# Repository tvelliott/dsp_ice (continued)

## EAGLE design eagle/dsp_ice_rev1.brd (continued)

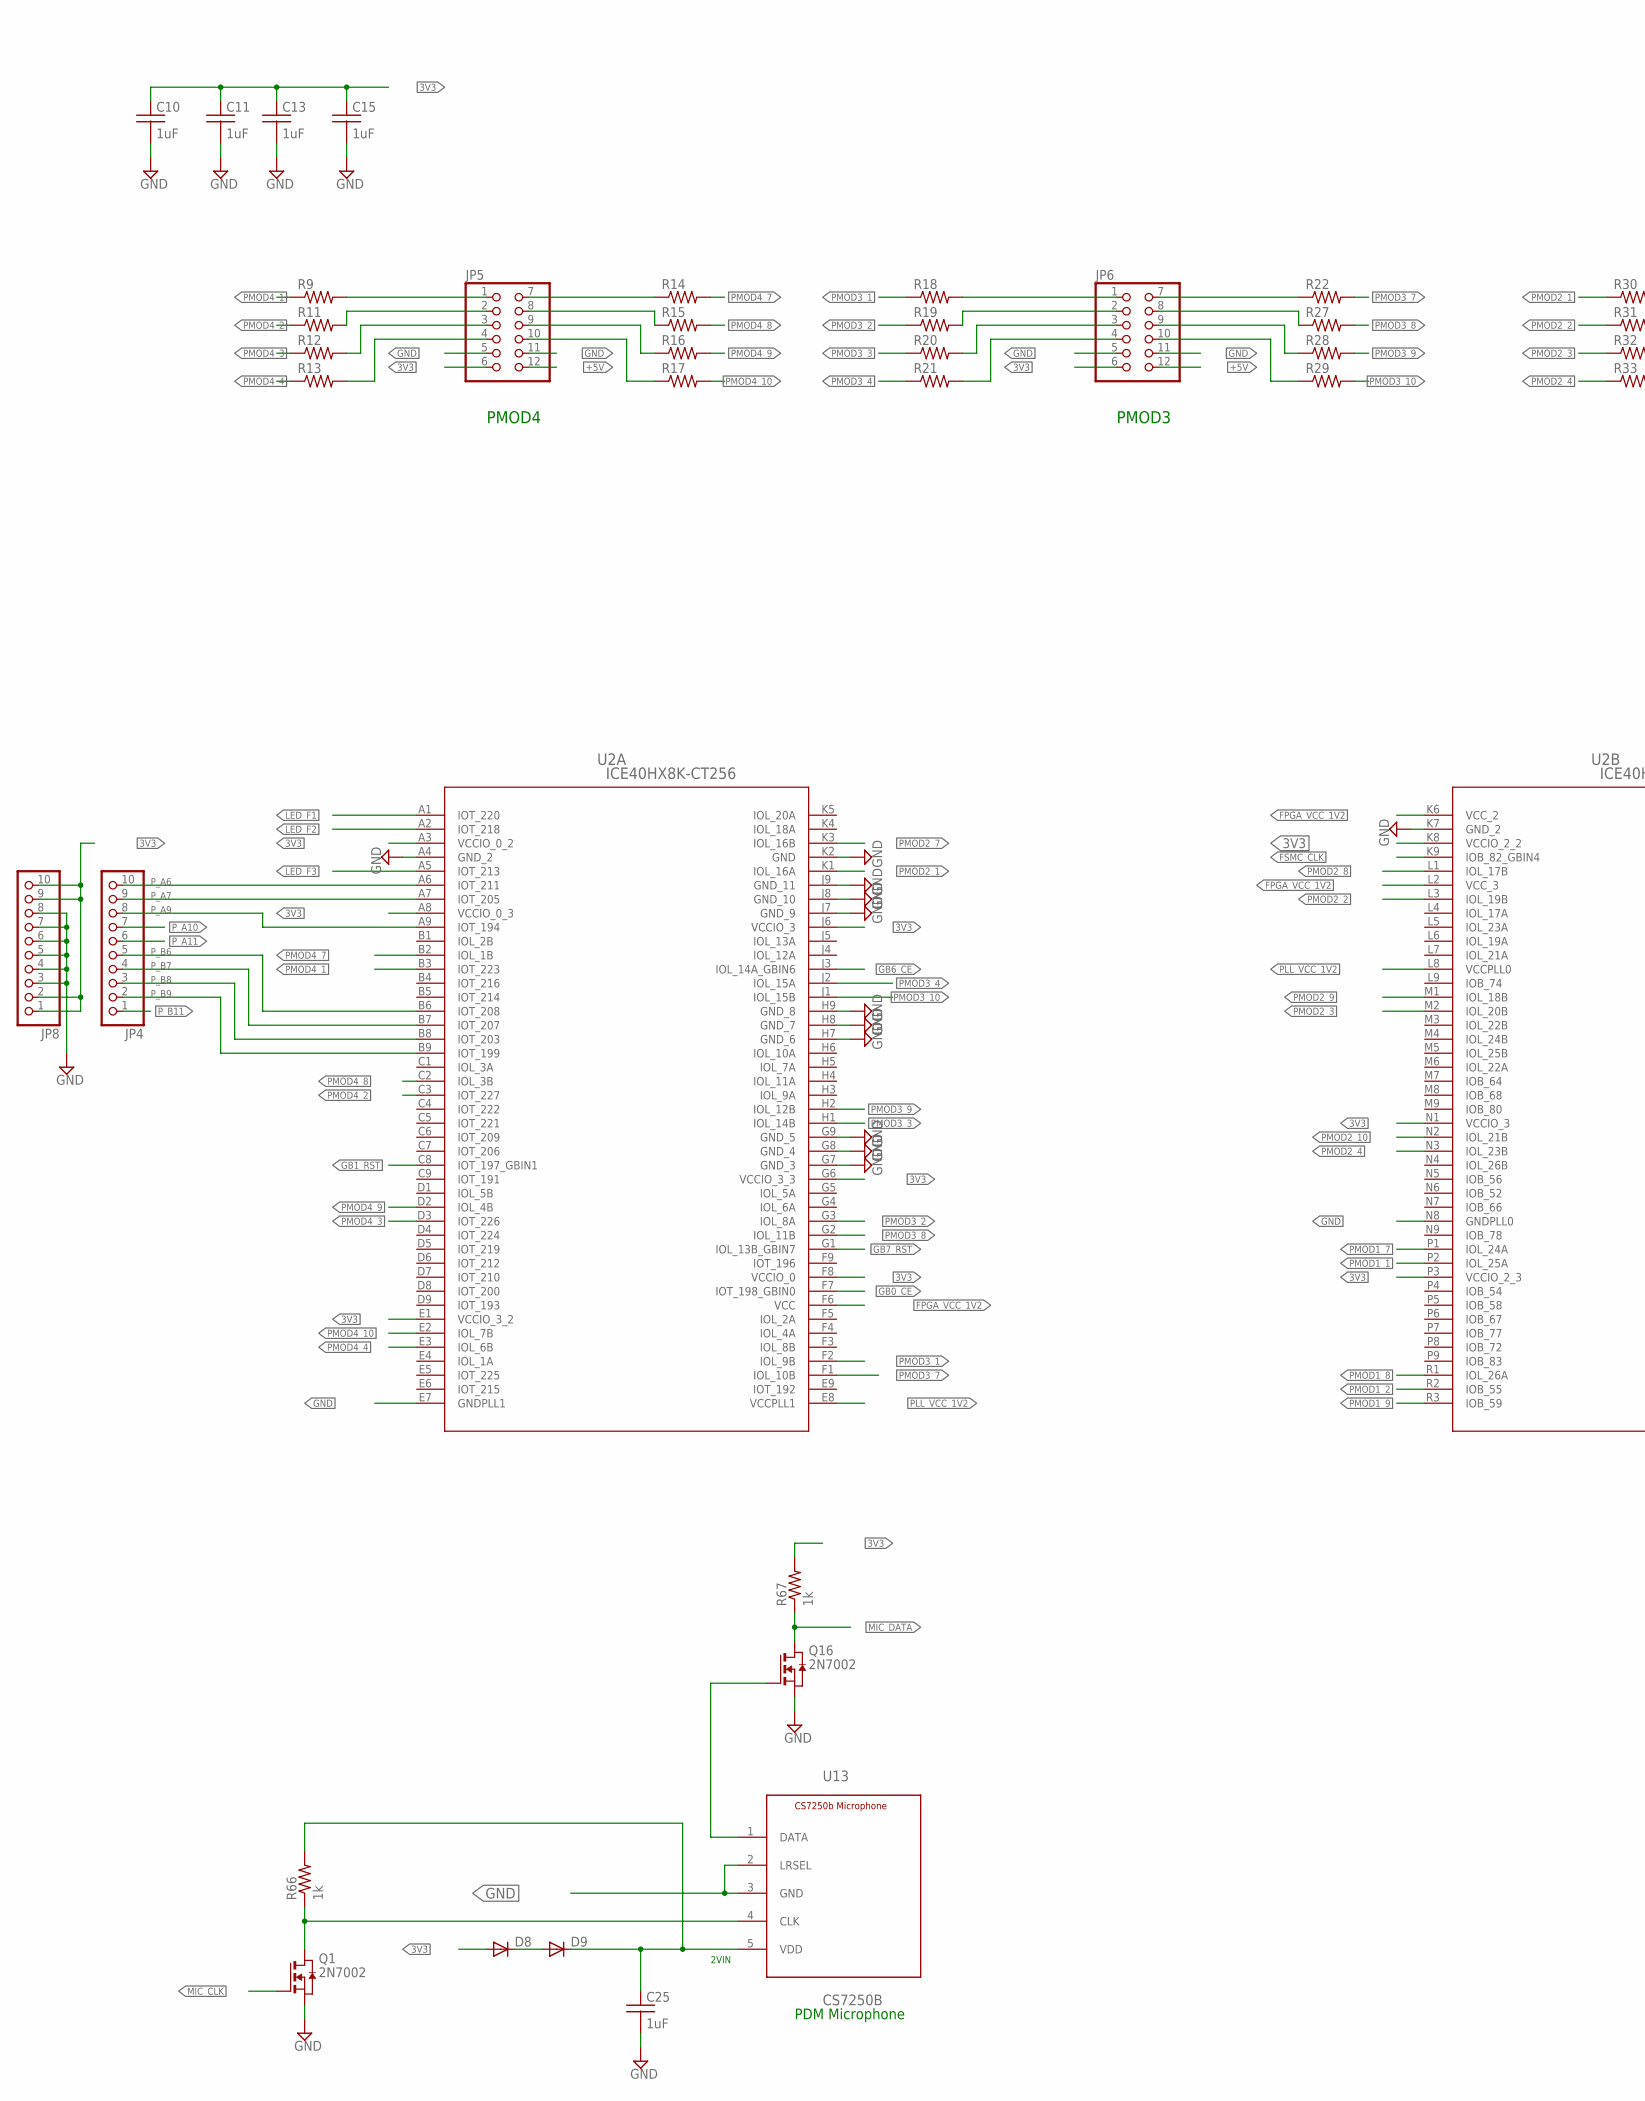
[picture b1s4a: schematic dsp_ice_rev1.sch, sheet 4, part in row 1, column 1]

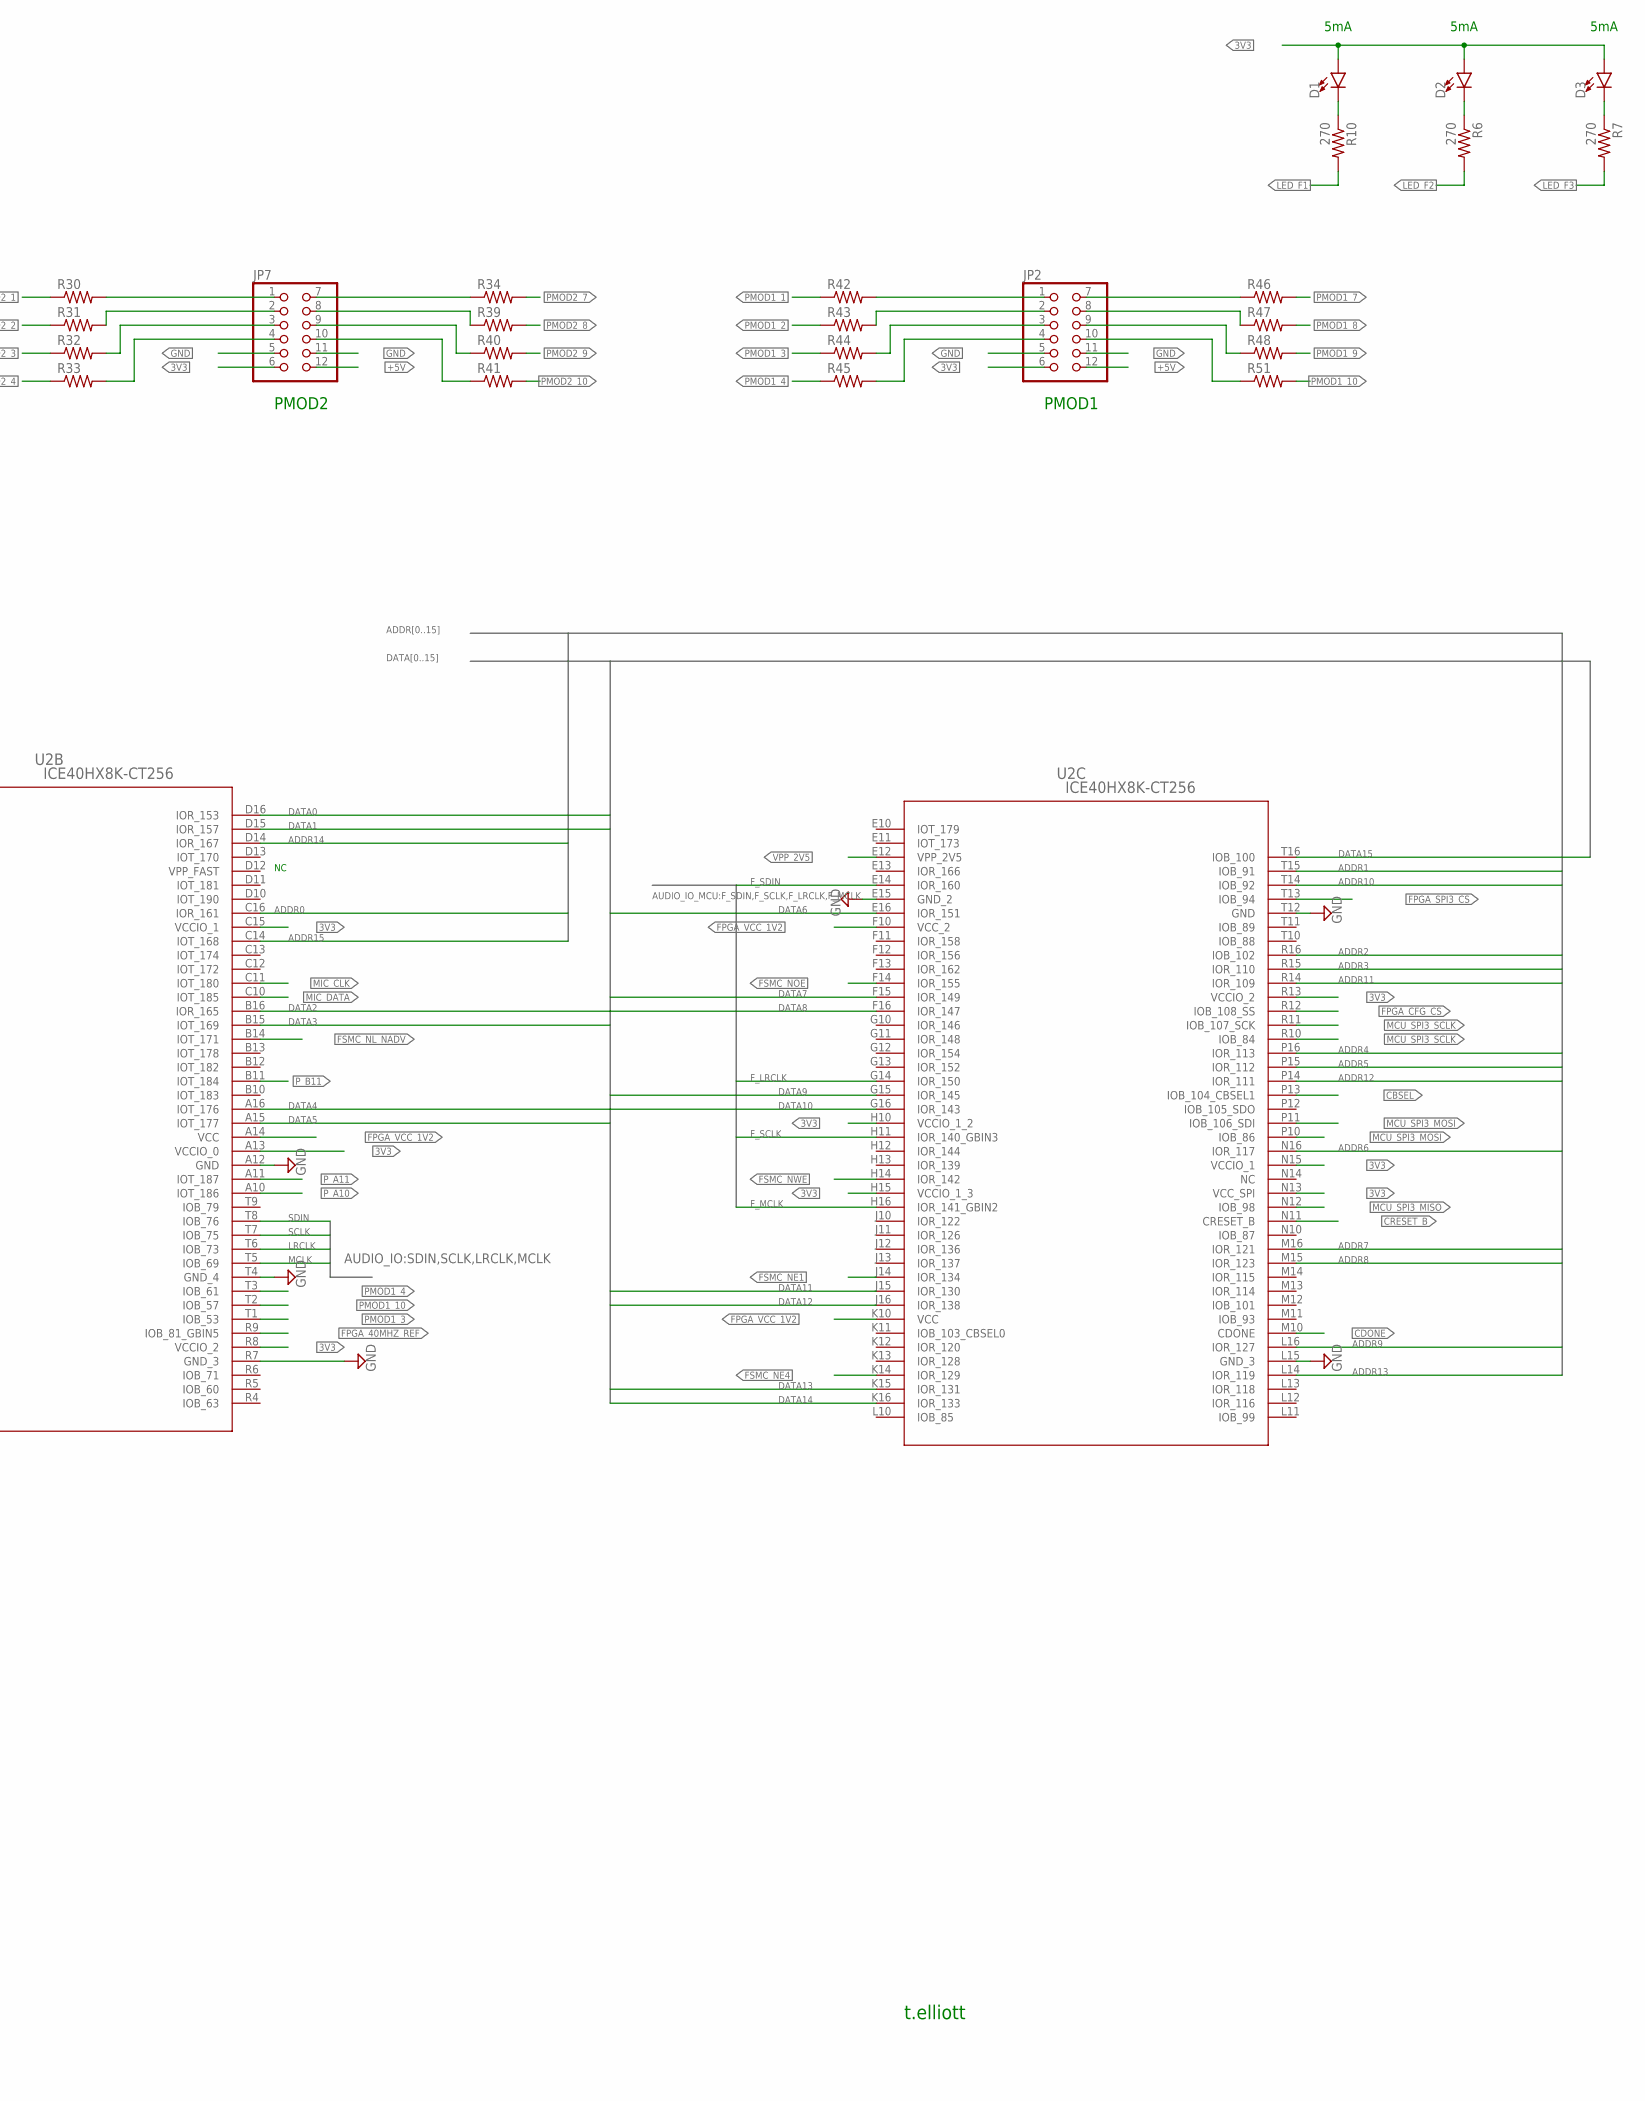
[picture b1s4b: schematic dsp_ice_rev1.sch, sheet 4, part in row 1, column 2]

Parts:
C10, C11, C13, C15, C25: 1uF; C0603
D1, D2, D3: LED1206; LED-1206
D8, D9: DIODE-MINIMELF; MINIMELF
JP2, JP5, JP6, JP7: PINHD-2X6; 2X06
JP4, JP8: PINHD-1X10; 1X10
Q1, Q16: 2N7002; SOT23_2N7002_PACKAGE
R6, R7, R10: 270; R0603
R9, R11, R12, R13, R14, R15, R16, R17, R18, R19, R20, R21, R22, R27, R28, R29, R30, R31, R32, R33, R34, R39, R40, R41, R42, R43, R44, R45, R46, R47, R48, R51: 10; R0603
R66, R67: 1k; R0603
U2: ICE40HX8K-CT256; CABGA256
U13: CS7250B; CS7250B-CAZR

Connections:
3V3: C10.1, C11.1, C13.1, C15.1, D1.A, D2.A, D3.A, D8.A, JP2.6 (11), JP5.6 (11), JP6.6 (11), JP7.6 (11), JP8.1, JP8.2, JP8.9, JP8.10, R67.2, U2.A3 (VCCIO_0_2), U2.A8 (VCCIO_0_3), U2.A13 (VCCIO_0), U2.C15 (VCCIO_1), U2.E1 (VCCIO_3_2), U2.F8 (VCCIO_0), U2.G6 (VCCIO_3_3), U2.H10 (VCCIO_1_2), U2.H15 (VCCIO_1_3), U2.J6 (VCCIO_3), U2.K8 (VCCIO_2_2), U2.N1 (VCCIO_3), U2.N13 (VCC_SPI), U2.N15 (VCCIO_1), U2.P3 (VCCIO_2_3), U2.R8 (VCCIO_2), U2.R13 (VCCIO_2); also elsewhere on the board
+5V: JP2.12, JP5.12, JP6.12, JP7.12; also elsewhere on the board
ADDR0: U2.C16 (IOR_161); also elsewhere on the board
ADDR1: U2.T15 (IOB_91); also elsewhere on the board
ADDR2: U2.R16 (IOB_102); also elsewhere on the board
ADDR3: U2.R15 (IOR_110); also elsewhere on the board
ADDR4: U2.P16 (IOR_113); also elsewhere on the board
ADDR5: U2.P15 (IOR_112); also elsewhere on the board
ADDR6: U2.N16 (IOR_117); also elsewhere on the board
ADDR7: U2.M16 (IOR_121); also elsewhere on the board
ADDR8: U2.M15 (IOR_123); also elsewhere on the board
ADDR9: U2.L16 (IOR_127); also elsewhere on the board
ADDR10: U2.T14 (IOB_92); also elsewhere on the board
ADDR11: U2.R14 (IOR_109); also elsewhere on the board
ADDR12: U2.P14 (IOR_111); also elsewhere on the board
ADDR13: U2.L14 (IOR_119); also elsewhere on the board
ADDR14: U2.D14 (IOR_167); also elsewhere on the board
ADDR15: U2.C14 (IOT_168); also elsewhere on the board
CBSEL: U2.P13 (IOB_104_CBSEL1); also elsewhere on the board
CDONE: U2.M10 (CDONE); also elsewhere on the board
CRESET_B: U2.N11 (CRESET_B); also elsewhere on the board
DATA0: U2.D16 (IOR_153); also elsewhere on the board
DATA1: U2.D15 (IOR_157); also elsewhere on the board
DATA2: U2.B16 (IOR_165); also elsewhere on the board
DATA3: U2.B15 (IOT_169); also elsewhere on the board
DATA4: U2.A16 (IOT_176); also elsewhere on the board
DATA5: U2.A15 (IOT_177); also elsewhere on the board
DATA6: U2.E16 (IOR_151); also elsewhere on the board
DATA7: U2.F15 (IOR_149); also elsewhere on the board
DATA8: U2.F16 (IOR_147); also elsewhere on the board
DATA9: U2.G15 (IOR_145); also elsewhere on the board
DATA10: U2.G16 (IOR_143); also elsewhere on the board
DATA11: U2.J15 (IOR_130); also elsewhere on the board
DATA12: U2.J16 (IOR_138); also elsewhere on the board
DATA13: U2.K15 (IOR_131); also elsewhere on the board
DATA14: U2.K16 (IOR_133); also elsewhere on the board
DATA15: U2.T16 (IOB_100); also elsewhere on the board
FPGA_40MHZ_REF: U2.R9 (IOB_81_GBIN5); also elsewhere on the board
FPGA_CFG_CS: U2.R12 (IOB_108_SS); also elsewhere on the board
FPGA_SPI3_CS: U2.T13 (IOB_94); also elsewhere on the board
FPGA_VCC_1V2: U2.A14 (VCC), U2.F6 (VCC), U2.F10 (VCC_2), U2.K6 (VCC_2), U2.K10 (VCC), U2.L2 (VCC_3); also elsewhere on the board
FSMC_CLK: U2.K9 (IOB_82_GBIN4); also elsewhere on the board
FSMC_NE1: U2.J14 (IOR_134); also elsewhere on the board
FSMC_NE4: U2.K14 (IOR_129); also elsewhere on the board
FSMC_NL_NADV: U2.B14 (IOT_171); also elsewhere on the board
FSMC_NOE: U2.F14 (IOR_155); also elsewhere on the board
FSMC_NWE: U2.H14 (IOR_142); also elsewhere on the board
F_LRCLK: U2.G14 (IOR_150); also elsewhere on the board
F_MCLK: U2.H16 (IOR_141_GBIN2); also elsewhere on the board
F_SCLK: U2.H11 (IOR_140_GBIN3); also elsewhere on the board
F_SDIN: U2.E14 (IOR_160); also elsewhere on the board
GB0_CE: U2.F7 (IOT_198_GBIN0)
GB1_RST: U2.C8 (IOT_197_GBIN1)
GB6_CE: U2.J3 (IOL_14A_GBIN6)
GB7_RST: U2.G1 (IOL_13B_GBIN7)
GND: C10.2, C11.2, C13.2, C15.2, C25.2, JP2.5 (9), JP2.11 (10), JP5.5 (9), JP5.11 (10), JP6.5 (9), JP6.11 (10), JP7.5 (9), JP7.11 (10), JP8.3, JP8.4, JP8.5, JP8.6, JP8.7, JP8.8, Q1.2 (S), Q16.2 (S), U2.A4 (GND_2), U2.A12 (GND), U2.E7 (GNDPLL1), U2.E15 (GND_2), U2.G7 (GND_3), U2.G8 (GND_4), U2.G9 (GND_5), U2.H7 (GND_6), U2.H8 (GND_7), U2.H9 (GND_8), U2.J7 (GND_9), U2.J8 (GND_10), U2.J9 (GND_11), U2.K2 (GND), U2.K7 (GND_2), U2.L15 (GND_3), U2.N8 (GNDPLL0), U2.R7 (GND_3), U2.T4 (GND_4), U2.T12 (GND), U13.2 (LRSEL), U13.3 (GND); also elsewhere on the board
LED_F1: R10.2, U2.A1 (IOT_220)
LED_F2: R6.2, U2.A2 (IOT_218)
LED_F3: R7.2, U2.A5 (IOT_213)
LRCLK: U2.T6 (IOB_73); also elsewhere on the board
MCLK: U2.T5 (IOB_69); also elsewhere on the board
MCU_SPI3_MISO: U2.N12 (IOB_98); also elsewhere on the board
MCU_SPI3_MOSI: U2.P10 (IOB_86), U2.P11 (IOB_106_SDI); also elsewhere on the board
MCU_SPI3_SCLK: U2.R10 (IOB_84), U2.R11 (IOB_107_SCK); also elsewhere on the board
MIC_CLK: Q1.1 (G), U2.C11 (IOT_180)
MIC_DATA: Q16.3 (D), R67.1, U2.C10 (IOT_185)
unnamed: D1.C, R10.1
unnamed: D2.C, R6.1
unnamed: D3.C, R7.1
unnamed: JP5.1, R9.2
unnamed: JP5.2 (3), R11.2
unnamed: JP5.3 (5), R12.2
unnamed: JP5.4 (7), R13.2
unnamed: JP5.10 (8), R17.1
unnamed: JP5.9 (6), R16.1
unnamed: JP5.8 (4), R15.1
unnamed: JP5.7 (2), R14.1
unnamed: JP6.1, R18.2
unnamed: JP6.2 (3), R19.2
unnamed: JP6.3 (5), R20.2
unnamed: JP6.4 (7), R21.2
unnamed: D8.C, D9.A
unnamed: JP6.7 (2), R22.1
unnamed: JP6.8 (4), R27.1
unnamed: JP6.9 (6), R28.1
unnamed: JP6.10 (8), R29.1
unnamed: C25.1, D9.C, R66.2, U13.5 (VDD)
unnamed: Q1.3 (D), R66.1, U13.4 (CLK)
unnamed: Q16.1 (G), U13.1 (DATA)
unnamed: JP7.1, R30.2
unnamed: JP7.2 (3), R31.2
unnamed: JP7.3 (5), R32.2
unnamed: JP7.4 (7), R33.2
unnamed: JP7.7 (2), R34.1
unnamed: JP7.8 (4), R39.1
unnamed: JP7.9 (6), R40.1
unnamed: JP7.10 (8), R41.1
unnamed: JP2.1, R42.2
unnamed: JP2.2 (3), R43.2
unnamed: JP2.3 (5), R44.2
unnamed: JP2.4 (7), R45.2
unnamed: JP2.7 (2), R46.1
unnamed: JP2.8 (4), R47.1
unnamed: JP2.9 (6), R48.1
unnamed: JP2.10 (8), R51.1
PLL_VCC_1V2: U2.E8 (VCCPLL1), U2.L8 (VCCPLL0); also elsewhere on the board
PMOD1_1: R42.1, U2.P2 (IOL_25A)
PMOD1_2: R43.1, U2.R2 (IOB_55)
PMOD1_3: R44.1, U2.T1 (IOB_53)
PMOD1_4: R45.1, U2.T3 (IOB_61)
PMOD1_7: R46.2, U2.P1 (IOL_24A)
PMOD1_8: R47.2, U2.R1 (IOL_26A)
PMOD1_9: R48.2, U2.R3 (IOB_59)
PMOD1_10: R51.2, U2.T2 (IOB_57)
PMOD2_1: R30.1, U2.K1 (IOL_16A)
PMOD2_2: R31.1, U2.L3 (IOL_19B)
PMOD2_3: R32.1, U2.M2 (IOL_20B)
PMOD2_4: R33.1, U2.N3 (IOL_23B)
PMOD2_7: R34.2, U2.K3 (IOL_16B)
PMOD2_8: R39.2, U2.L1 (IOL_17B)
PMOD2_9: R40.2, U2.M1 (IOL_18B)
PMOD2_10: R41.2, U2.N2 (IOL_21B)
PMOD3_1: R18.1, U2.F2 (IOL_9B)
PMOD3_2: R19.1, U2.G3 (IOL_8A)
PMOD3_3: R20.1, U2.H1 (IOL_14B)
PMOD3_4: R21.1, U2.J2 (IOL_15A)
PMOD3_7: R22.2, U2.F1 (IOL_10B)
PMOD3_8: R27.2, U2.G2 (IOL_11B)
PMOD3_9: R28.2, U2.H2 (IOL_12B)
PMOD3_10: R29.2, U2.J1 (IOL_15B)
PMOD4_1: R9.1, U2.B3 (IOT_223)
PMOD4_2: R11.1, U2.C3 (IOT_227)
PMOD4_3: R12.1, U2.D3 (IOT_226)
PMOD4_4: R13.1, U2.E3 (IOL_6B)
PMOD4_7: R14.2, U2.B2 (IOL_1B)
PMOD4_8: R15.2, U2.C2 (IOL_3B)
PMOD4_9: R16.2, U2.D2 (IOL_4B)
PMOD4_10: R17.2, U2.E2 (IOL_7B)
P_A6: JP4.10, U2.A6 (IOT_211)
P_A7: JP4.9, U2.A7 (IOT_205)
P_A9: JP4.8, U2.A9 (IOT_194)
P_A10: JP4.7, U2.A10 (IOT_186)
P_A11: JP4.6, U2.A11 (IOT_187)
P_B6: JP4.5, U2.B6 (IOT_208)
P_B7: JP4.4, U2.B7 (IOT_207)
P_B8: JP4.3, U2.B8 (IOT_203)
P_B9: JP4.2, U2.B9 (IOT_199)
P_B11: JP4.1, U2.B11 (IOT_184)
SCLK: U2.T7 (IOB_75); also elsewhere on the board
SDIN: U2.T8 (IOB_76); also elsewhere on the board
VPP_2V5: U2.E12 (VPP_2V5); also elsewhere on the board
VPP_FAST: U2.D12 (VPP_FAST)

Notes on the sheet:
5mA
PMOD4
PMOD3
PMOD2
PMOD1
t.elliott
PDM Microphone
2VIN

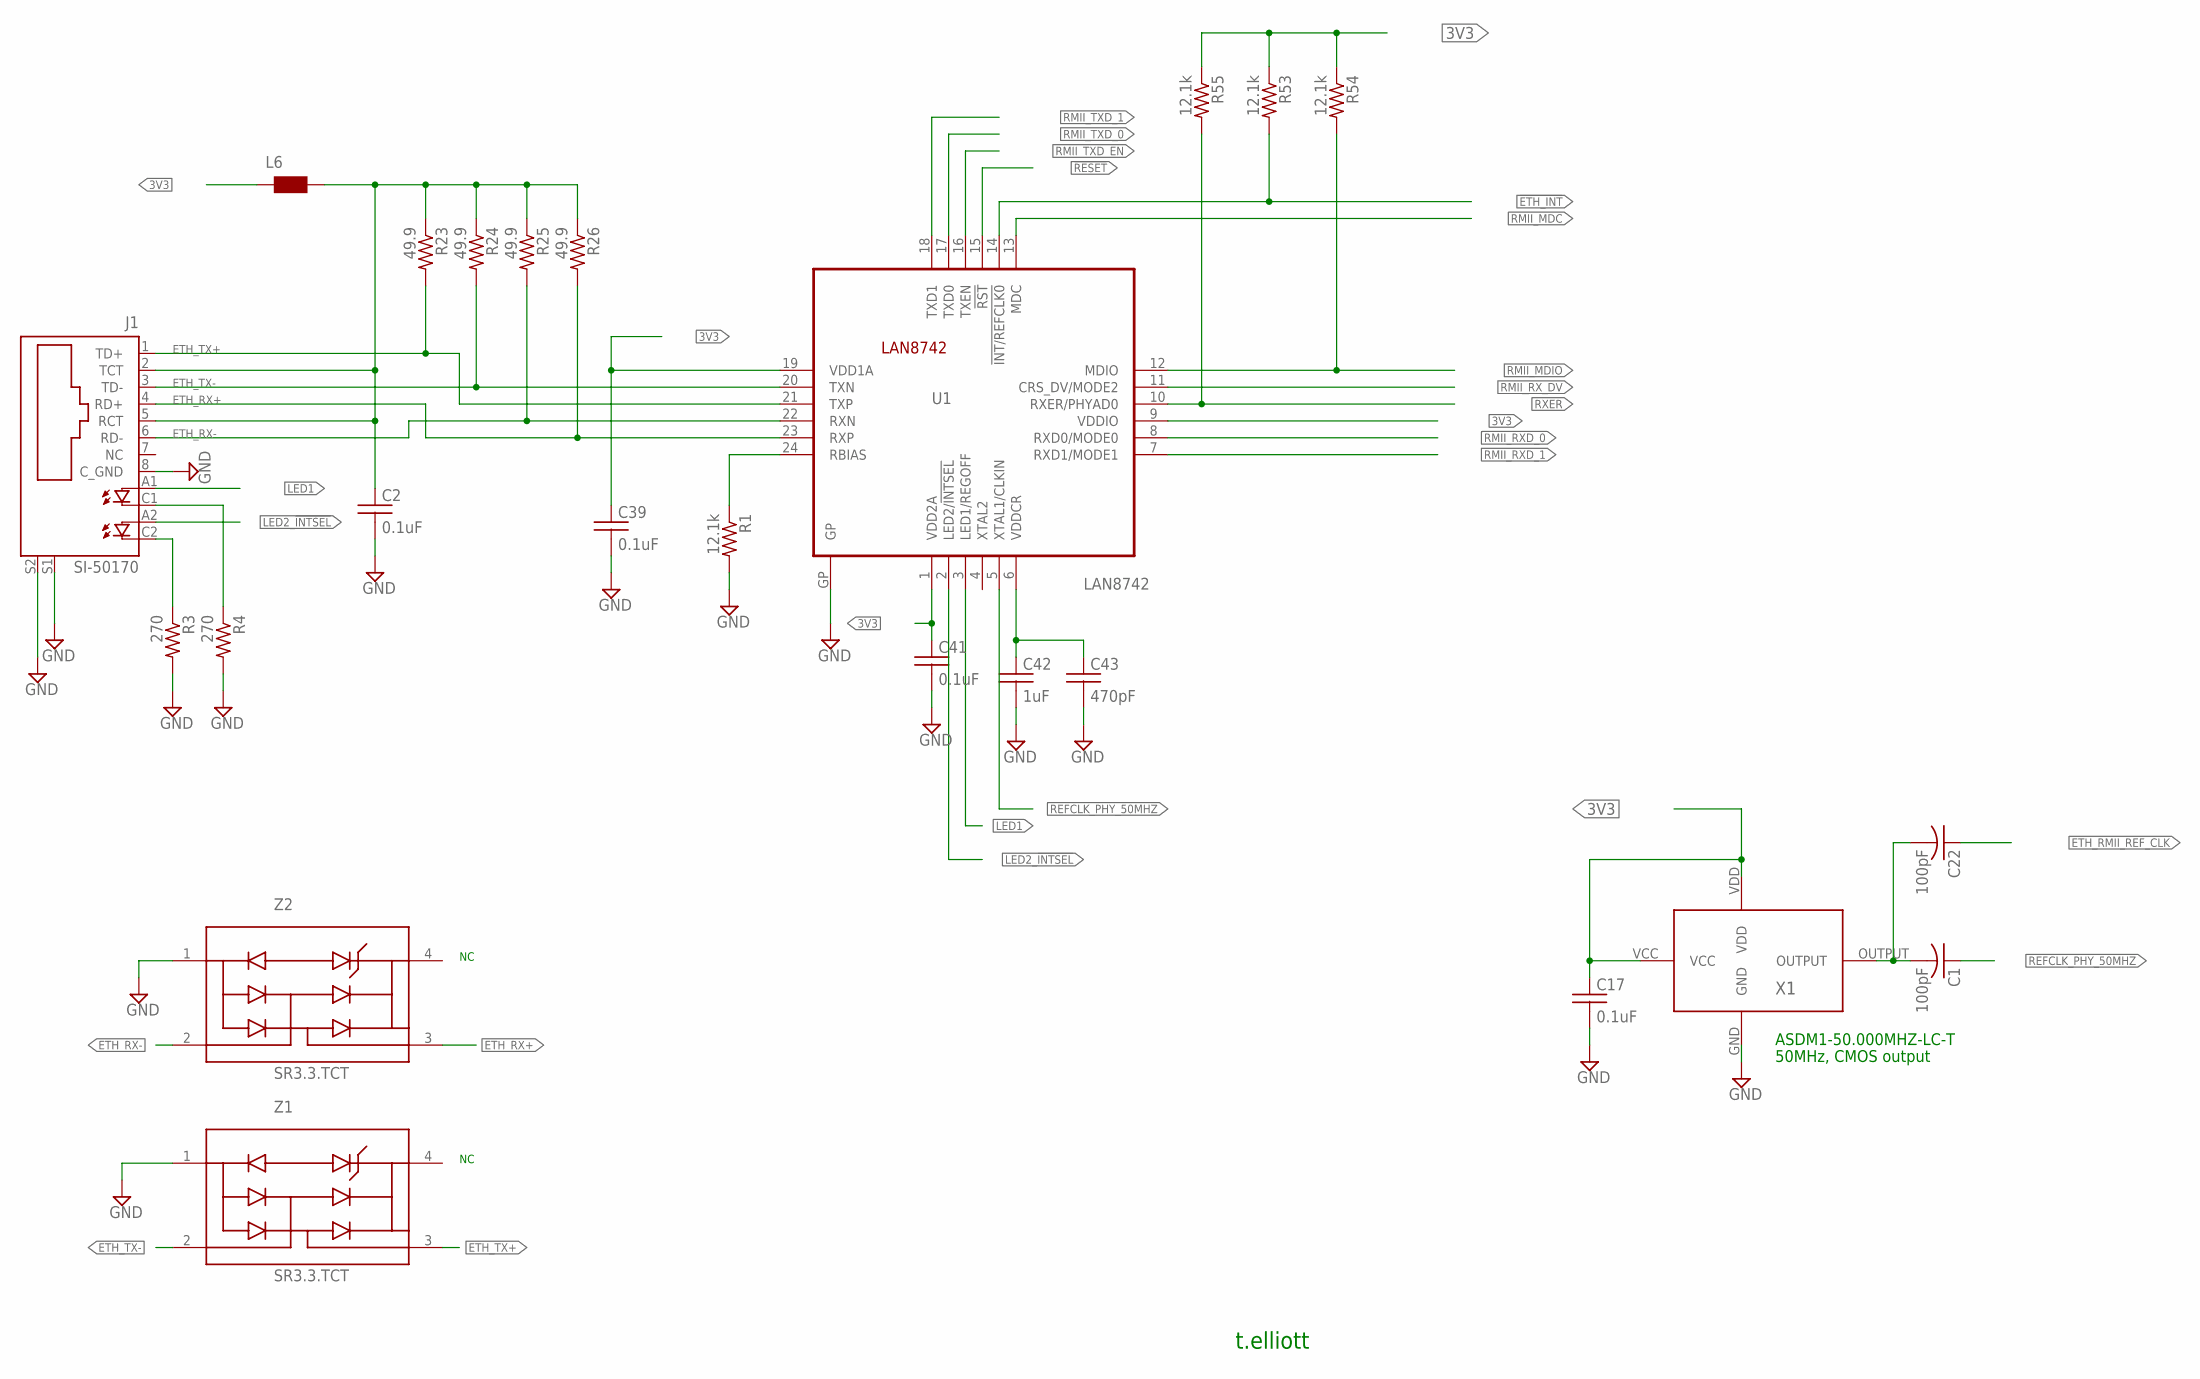
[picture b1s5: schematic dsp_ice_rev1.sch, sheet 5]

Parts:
C1, C22: 100pF; C0603
C2, C17, C39, C41: 0.1uF; C0603
C42: 1uF; C0603
C43: 470pF; C0603
J1: SI-50170
L6: WE-CBF_0603; 0603
R1, R53, R54, R55: 12.1k; R0603
R3, R4: 270; R0603
R23, R24, R25, R26: 49.9; R0603
U1: LAN8742; QFN-24
X1: ASDM1-50.000MHZ-LC-T; CRYSTAL_2.5_2MM
Z1, Z2: SR3.3.TCT; SR2.8.TCT_1PRIMARY

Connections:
3V3: C17.1, C39.1, C41.1, L6.1, R53.1, R54.1, R55.1, U1.1 (VDD2A), U1.9 (VDDIO), U1.19 (VDD1A), X1.VCC, X1.VDD; also elsewhere on the board
!ETH_INT: R53.2, U1.14 (!INT/REFCLK0); also elsewhere on the board
!RESET: U1.15 (!RST); also elsewhere on the board
ETH_RMII_REF_CLK: C22.1; also elsewhere on the board
ETH_RX+: J1.4 (RD+), R26.2, U1.23 (RXP), Z2.3 (I/O)
ETH_RX-: J1.6 (RD-), R25.2, U1.22 (RXN), Z2.2 (I/O)
ETH_TX+: J1.1 (TD+), R23.2, U1.21 (TXP), Z1.3 (I/O)
ETH_TX-: J1.3 (TD-), R24.2, U1.20 (TXN), Z1.2 (I/O)
GND: C2.2, C17.2, C39.2, C41.2, C42.2, C43.2, J1.8 (C_GND), J1.S1, J1.S2, R1.2, R3.2, R4.2, U1.GP, X1.GND, Z1.1 (GND), Z2.1 (GND); also elsewhere on the board
LED1: J1.A1 (A), U1.3 (LED1/REGOFF)
LED2_!INTSEL: J1.A2 (A1), U1.2 (LED2/!INTSEL)
unnamed: C1.2, C22.2, X1.OUTPUT
unnamed: C42.1, C43.1, U1.6 (VDDCR)
unnamed: J1.C2 (C1), R3.1
unnamed: R1.1, U1.24 (RBIAS)
unnamed: C2.1, J1.2 (TCT), J1.5 (RCT), L6.2, R23.1, R24.1, R25.1, R26.1
unnamed: J1.C1 (C), R4.1
REFCLK_PHY_50MHZ: C1.1, U1.5 (XTAL1/CLKIN)
RMII_MDC: U1.13 (MDC); also elsewhere on the board
RMII_MDIO: R54.2, U1.12 (MDIO); also elsewhere on the board
RMII_RXD_0: U1.8 (RXD0/MODE0); also elsewhere on the board
RMII_RXD_1: U1.7 (RXD1/MODE1); also elsewhere on the board
RMII_RX_DV: U1.11 (CRS_DV/MODE2); also elsewhere on the board
RMII_TXD_0: U1.17 (TXD0); also elsewhere on the board
RMII_TXD_1: U1.18 (TXD1); also elsewhere on the board
RMII_TXD_EN: U1.16 (TXEN); also elsewhere on the board
RXER: R55.2, U1.10 (RXER/PHYAD0)

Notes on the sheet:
ASDM1-50.000MHZ-LC-T
50MHz, CMOS output
t.elliott

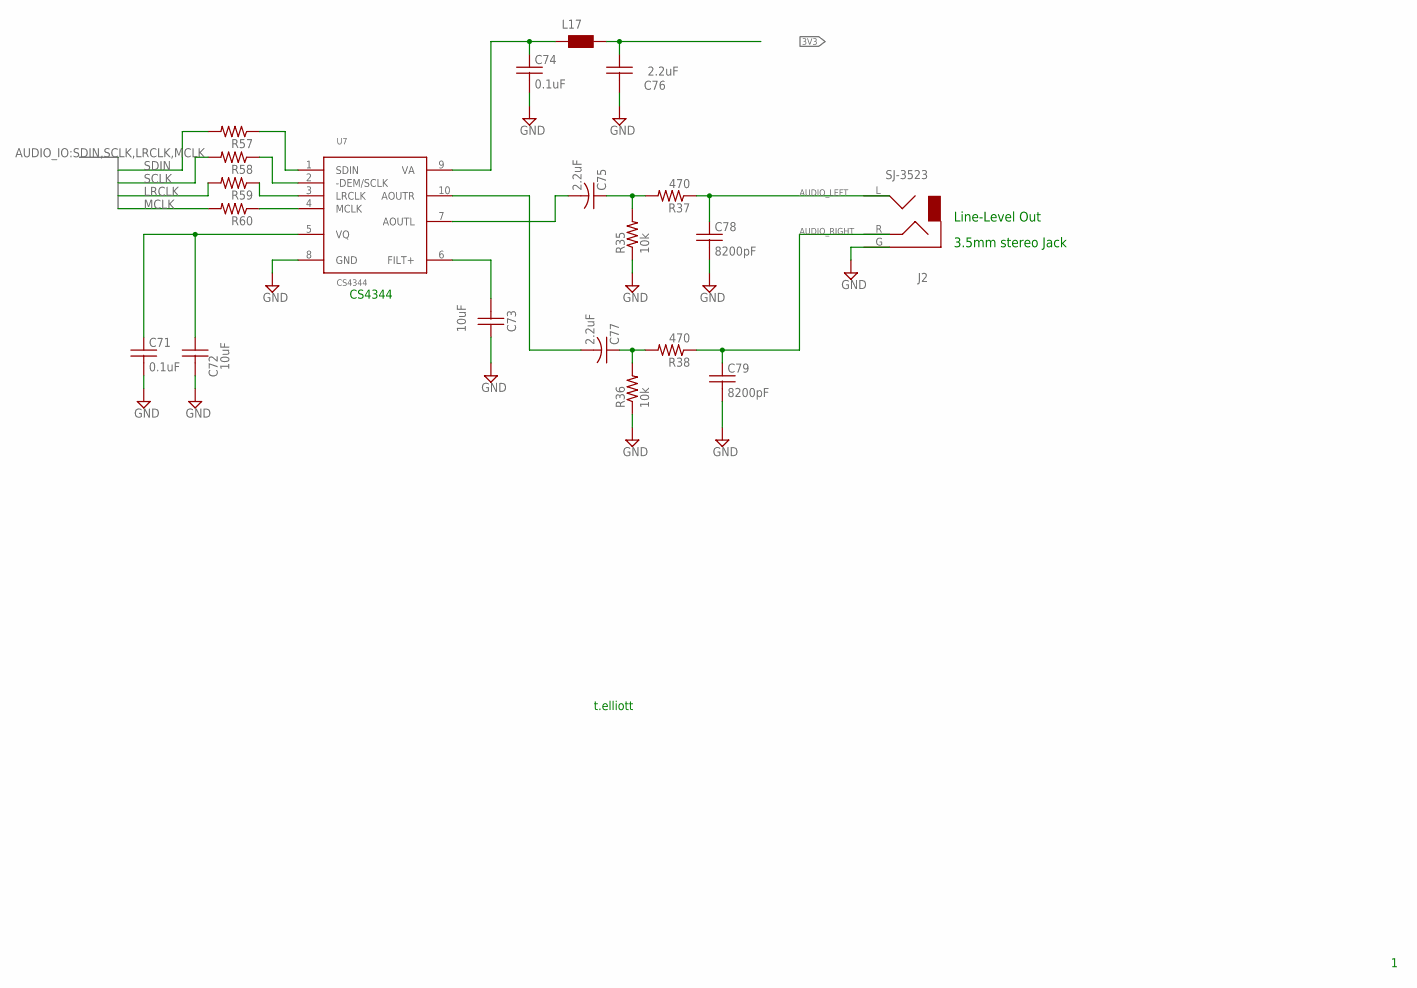
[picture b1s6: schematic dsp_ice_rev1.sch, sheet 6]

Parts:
C71, C74: 0.1uF; C0603
C72, C73: 10uF; C0805
C75, C76, C77: 2.2uF; C0805
C78, C79: 8200pF; C0603
J2: SJ-3523
L17: WE-CBF_0603; 0603
R35, R36: 10k; R0402
R37, R38, R57, R58, R59, R60: 470; R0402
U7: CS4344; MSOP10

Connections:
3V3: C76.1, L17.2; also elsewhere on the board
AUDIO_LEFT: C79.1, J2.R, R38.1
AUDIO_RIGHT: C78.1, J2.L, R37.1
GND: C71.2, C72.2, C73.1, C74.2, C76.2, C78.2, C79.2, J2.G, R35.1, R36.1, U7.8 (GND); also elsewhere on the board
LRCLK: R59.2; also elsewhere on the board
MCLK: R60.2; also elsewhere on the board
unnamed: C77.2, U7.10 (AOUTR)
unnamed: R60.1, U7.4 (MCLK)
unnamed: R59.1, U7.3 (LRCLK)
unnamed: R58.1, U7.2 (-DEM/SCLK)
unnamed: R57.1, U7.1 (SDIN)
unnamed: C73.2, U7.6 (FILT+)
unnamed: C71.1, C72.1, U7.5 (VQ)
unnamed: C75.2, U7.7 (AOUTL)
unnamed: C75.1, R35.2, R37.2
unnamed: C77.1, R36.2, R38.2
unnamed: C74.1, L17.1, U7.9 (VA)
SCLK: R58.2; also elsewhere on the board
SDIN: R57.2; also elsewhere on the board

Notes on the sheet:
t.elliott
CS4344
Line-Level Out
3.5mm stereo Jack

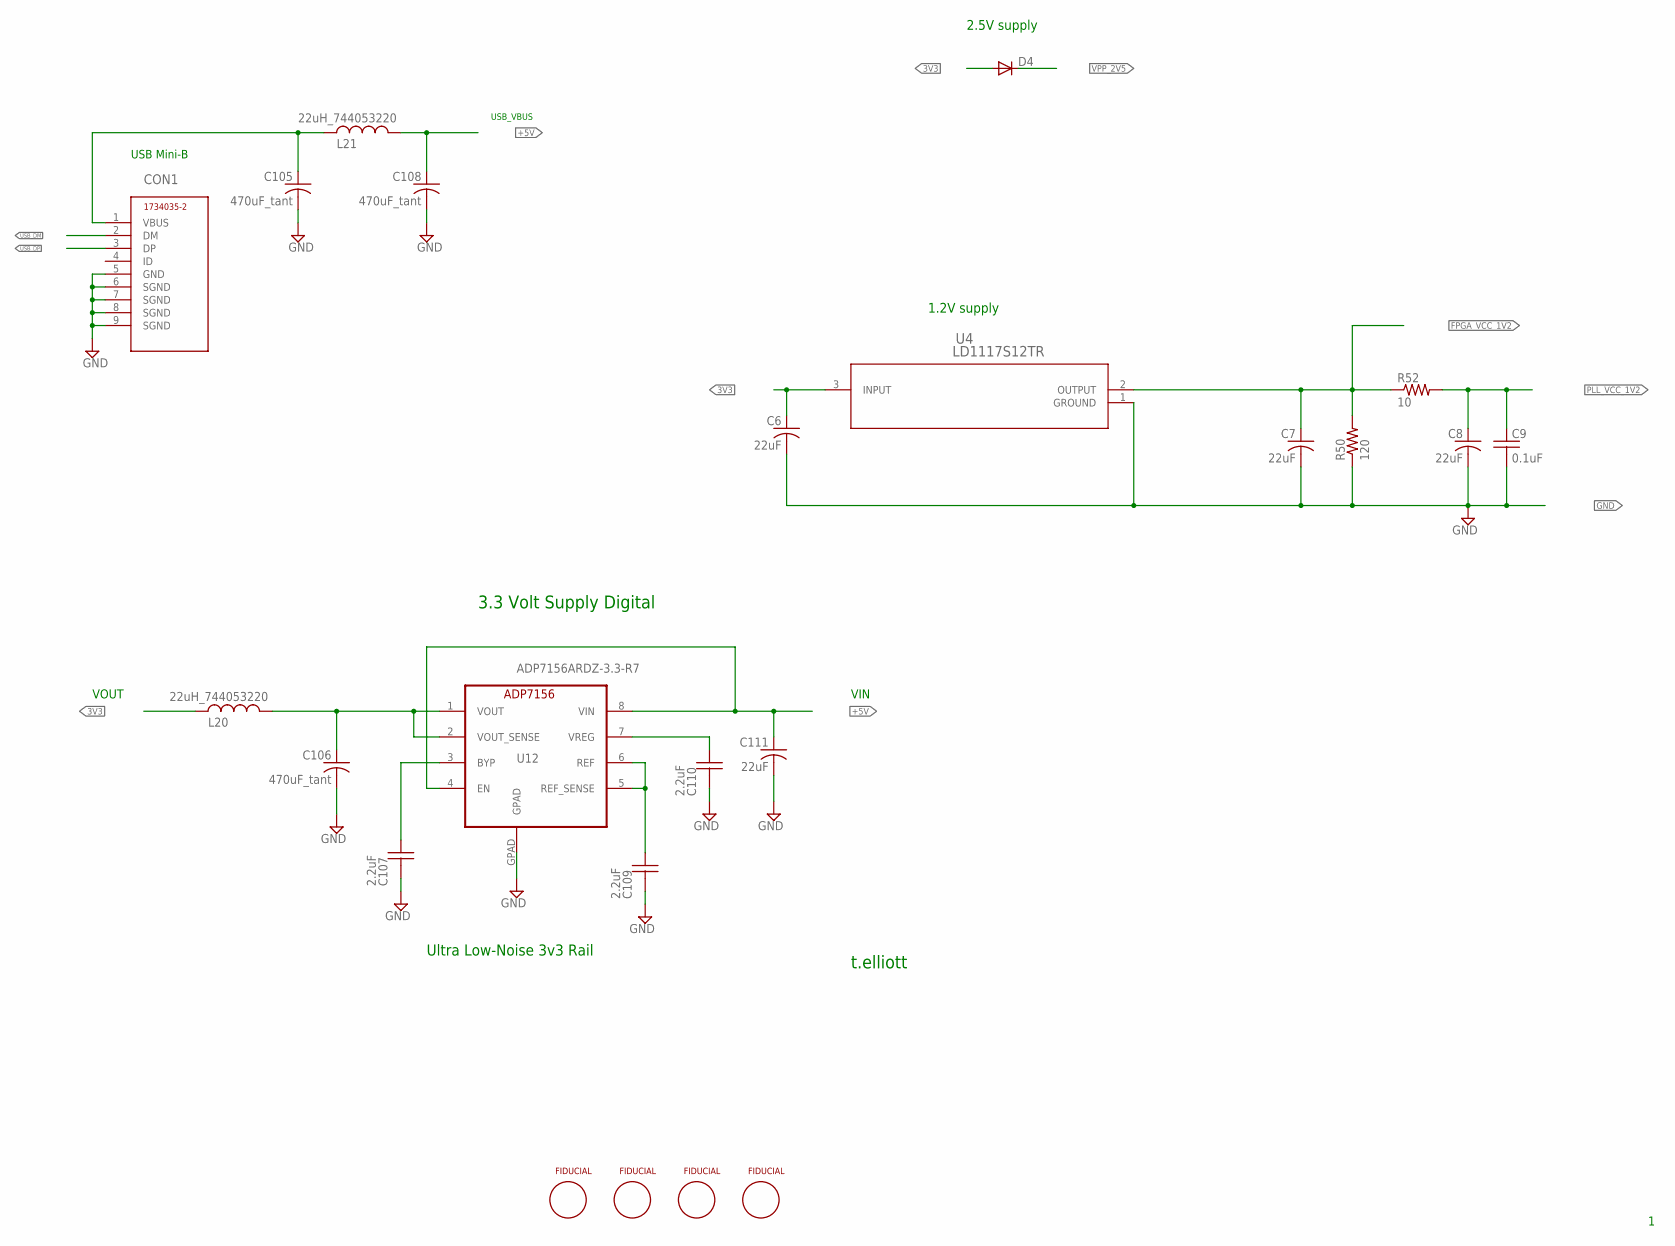
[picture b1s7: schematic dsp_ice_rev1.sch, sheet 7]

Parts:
C6, C7, C8, C111: 22uF; 1210K
C9: 0.1uF; C0603
C105, C106, C108: 470uF_tant; 1210K
C107, C109, C110: 2.2uF; C0805
CON1: 1734035-2
D4: DIODE-MINIMELF; MINIMELF
FID1, FID2, FID3, FID4: FIDUCIALSMD; FIDUCIAL
L20, L21: 22uH_744053220; POWER-CHOKE_WE-TPC
R50: 120; R0603
R52: 10; R0603
U4: LD1117S12TR; SOT-223
U12: ADP7156ARDZ-3.3-R7; SO8

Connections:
3V3: C6.A, D4.A, L20.2, U4.3 (INPUT); also elsewhere on the board
+5V: C108.A, C111.A, L21.1, U12.4 (EN), U12.8 (VIN); also elsewhere on the board
FPGA_VCC_1V2: C7.A, R50.2, R52.1, U4.2 (OUTPUT); also elsewhere on the board
GND: C6.C, C7.C, C8.C, C9.2, C105.C, C106.C, C107.2, C108.C, C109.2, C110.2, C111.C, CON1.5 (GND), CON1.6 (SGND), CON1.7 (SGND), CON1.8 (SGND), CON1.9 (SGND), R50.1, U4.1 (GROUND), U12.GPAD; also elsewhere on the board
unnamed: C105.A, CON1.1 (VBUS), L21.2
unnamed: C106.A, L20.1, U12.1 (VOUT), U12.2 (VOUT_SENSE)
unnamed: C109.1, U12.5 (REF_SENSE), U12.6 (REF)
unnamed: C110.1, U12.7 (VREG)
unnamed: C107.1, U12.3 (BYP)
PLL_VCC_1V2: C8.A, C9.1, R52.2; also elsewhere on the board
USB_DM: CON1.2 (DM); also elsewhere on the board
USB_DP: CON1.3 (DP); also elsewhere on the board
VPP_2V5: D4.C; also elsewhere on the board

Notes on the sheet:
t.elliott
VIN
VOUT
3.3 Volt Supply Digital
USB Mini-B
USB_VBUS
1.2V supply
2.5V supply
Ultra Low-Noise 3v3 Rail

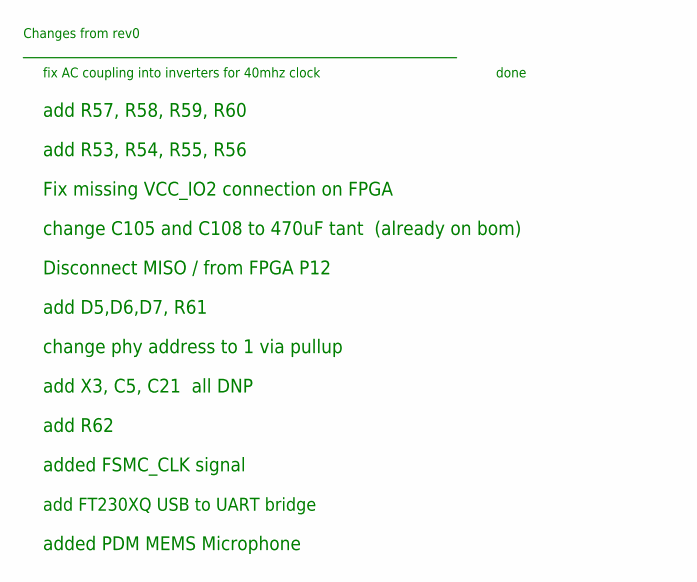
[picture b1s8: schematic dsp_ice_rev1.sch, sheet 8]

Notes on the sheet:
fix AC coupling into inverters for 40mhz clock
Changes from rev0
done
add R57, R58, R59, R60
add R53, R54, R55, R56
Fix missing VCC_IO2 connection on FPGA
change C105 and C108 to 470uF tant (already on bom)
Disconnect MISO / from FPGA P12
add D5,D6,D7, R61
change phy address to 1 via pullup
add X3, C5, C21 all DNP
add R62
added FSMC_CLK signal
add FT230XQ USB to UART bridge
added PDM MEMS Microphone
